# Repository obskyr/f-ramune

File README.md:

# F-Ramune

F-Ramune is a device that lets you test and program 28-pin FRAM chips (e.g. the FM1808 family)! It lets you:

* Test that a chip is genuine FRAM!
* Test that all of the memory cells of an FRAM chip work!
* Identify a memory chip (size, non-volatility, etc.)
* Read from an FRAM chip!
* Write to an FRAM chip!

It features a reprogrammable pushbutton that lets you quickly test chips – out of the box, it's set to check that a chip is 32 KiB of genuine FRAM in full working order – and a serial interface with accompanying software that lets you program your memory chips from your PC.

I made this to test FM1808s of dubious (i.e. cheap Chinese) origin so that the [Game Boy cartridge immortalization mod](https://www.tindie.com/products/obskyr/save-immortalizer-kit-for-game-boy/) would become more feasible and accessible. I expect that to be the main use of F-Ramune, but it's written in an extensible fashion – if you want to test or program FRAM (or SRAM!) in a different form factor or pinout, not much needs to be changed.

## Getting started

Since F-Ramune is a physical device, you'll first need to build that device. Instructions for this can be found in the [hardware directory](hardware) of the repo. At the moment, there's no PCB version, so it's fairly involved – you have to manually route it on stripboard or breadboard – but it's more than doable.

Once you've built the device, you need to upload the firmware to it. For user-friendliness, F-Ramune's firmware is Arduino-based! Open `software.ino` (in the [`software` directory](software)) in the [Arduino IDE](https://www.arduino.cc/en/main/software), set the board to "Arduino Nano", and click the "upload" button. Bam! Your F-Ramune is now ready to go!

## How to test a chip

Put the chip you want to test in the socket. Press the button to test the chip. Out of the box, upon pressing the button, the LEDs will possibly flash back and forth a bit while testing, and finally indicate:

* **Red** if the chip is 32 KiB of genuine FRAM.
* **Red and green** if the chip is genuine, but faulty memory cells were found.
* **Green** if the chip is 32 KiB of genuine FRAM.

The function of the button can be reprogrammed in [`software.ino`](software/software.ino), if you'd like to check for other traits.

## How to program or analyze a chip

Plug the F-Ramune Arduino into your PC, and put the chip you want to test in the socket. Using the command-line program `framune.py` (found in the `software` directory; requires [Python 3](https://www.python.org/downloads/)) , you can read from, write to, and analyze the properties of the chip. Run `framune.py --help` for details.

## Cool!

F-Ramune is just one part of a larger project, and it's fairly niche, so my instructions here are more terse than they usually are. But fear not! If you have any questions, there are any issues, or you just want to talk, you can contact me in the following ways:

* [@obskyr](https://twitter.com/obskyr) on Twitter, or
* [E-mail](mailto:powpowd@gmail.com) me!

For a quick response, writing to me on Twitter is your best bet. If you built F-Ramune, especially, I would *love* to hear about it!

Enjoy! ☆

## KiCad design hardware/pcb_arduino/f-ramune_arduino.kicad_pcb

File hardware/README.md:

# The F-Ramune hardware

As of yet, there's no PCB version of F-Ramune, but here are some instructions for building it on stripboard or breadboard!

The bill of materials is as following:

| Part                             | Description               | Number required |
| ----------------------------     | ------------------------- | --------------- |
| Arduino Nano                     |                           | 1               |
| ZIF Socket with DIP-28 footprint | To fit SMD parts a [SOIC-28 ZIF socket](https://www.adafruit.com/product/1281). To also be compatible with DIP chips, a DIP-28 ZIF socket can be used as the bottom layer in a… socket cake. | 1
| 74HC595                          | 8-bit SIPO shift register | 2               |
| IRL520N                          | N-channel MOSFET          | 1               |
| Green LED                        |                           | 1               |
| Red LED                          |                           | 1               |
| Pushbutton                       |                           | 1               |
| 10 kΩ resistor                   |                           | 1               |
| 100 Ω resistor                   |                           | 1               |
| 330 Ω resistor                   |                           | 2               |

## Tips for all versions

The schematic specifies the transistor to be an IRL520N, but **any N-channel MOSFET with an I<sub>D</sub>** (drain current) **of 200 mA or higher, a V<sub>GS</sub>** (gate threshold) **of 4.5 V or lower and an R<sub>DS(ON)</sub>** (on-resistance) **of 1 Ω or lower works**. The V<sub>GS</sub> requirement is for ~5 V logic signals to work. The R<sub>DS(ON)</sub> of 1 Ω is calculated based on an assumed max supply current for the memory chip of 200 mA and a max allowable voltage drop of 0.2 V (0.2 A / 0.2 V = 1 Ω). Using a more realistic max supply current of 140 mA and/or a more forgiving voltage drop limit, you can arrive at a higher max R<sub>DS(ON)</sub>, and it'll probably still work fine – albeit with less leeway. If you've got MOSFETs lying around, check out their datasheets and see if they're reasonably close to the requirements!

<!-- For the eventual PCB version:
## PCB

### Tips for the PCB version

* The schematic specifies an 18.432 MHz crystal, but if you've got a 16 MHz crystal lying around, you can use that – it'll just make the serial communication less reliable (0% timing error for 18.432 MHz vs. ~3.5% error for 16). This might still work fine, but it's possible it'll cause trouble with some serial adapters. 
-->

## Stripboard

There's no layout diagram for building F-Ramune on stripboard (since apparently there's no good digital stripboard design program!?), but it's a very reliable and permanent way to build it, so why not give it a shot? Using [the schematic](breadboard-schematic.png), you can put together something most respectable. Here's my finished stripboard:

Don't make the mistake I did and leave too little space for the socket – preferably, solder in whatever socket you're using *before* any wires. Measure twice, cut once, y'know?

## Breadboard

I wouldn't recommend breadboarding F-Ramune – breadboards are unreliable, and the device uses high-speed signals and has to be quite picky with voltages. If you would like to try, though, the breadboard schematic and layout can be found in `breadboard.fzz`, which is a [Fritzing](http://fritzing.org/) file. Either install Fritzing and open that file, or take a gander at the image versions of [the schematic](breadboard-schematic.png) and [the layout diagram](breadboard.png). The layout is somewhat optimistically routed, so some spur-of-the-moment re-routings may need to be done as space gets tight. Here's the finished product:

### Tips for breadboarding F-Ramune

* Use a high-quality breadboard! Although FRAM chips consume next to no current, SRAM chips can consume up to 140 mA. Channeling that much via a breadboard with poor connections and bizarrely resistive power rails is a fool's errand – I learned this the hard way.
* If you're using a breadboard of lesser quality, keep the following in mind:
    * When you insert a wire or a pin, make sure it feels like it's being gripped (and before you insert an IC, check those holes with a wire first). If it doesn't, that hole may be intermittent or flat-out broken. You can remedy this by using a different hole on the same row, replacing the strip on that particular row, or [jamming a resistor leg into it](https://twitter.com/obskyr/status/1096047043683012609).
    * You may need to run wires directly to the memory chip's V+ and ground pins from the holes right by the Arduino, since going via the power rails might prove too high-resistance. Adding more bridge wires (like the ones on the far right in the breadboard diagram) may also help, albeit not as much.
* The pins on a TO-220 package such as the MOSFET here are highly destructive to breadboard holes. Use a gripping implement to turn the thin part of the pins 45–90° before inserting it, so the pins don't get gripped lengthwise and bend the breadboard's connectors out of shape.

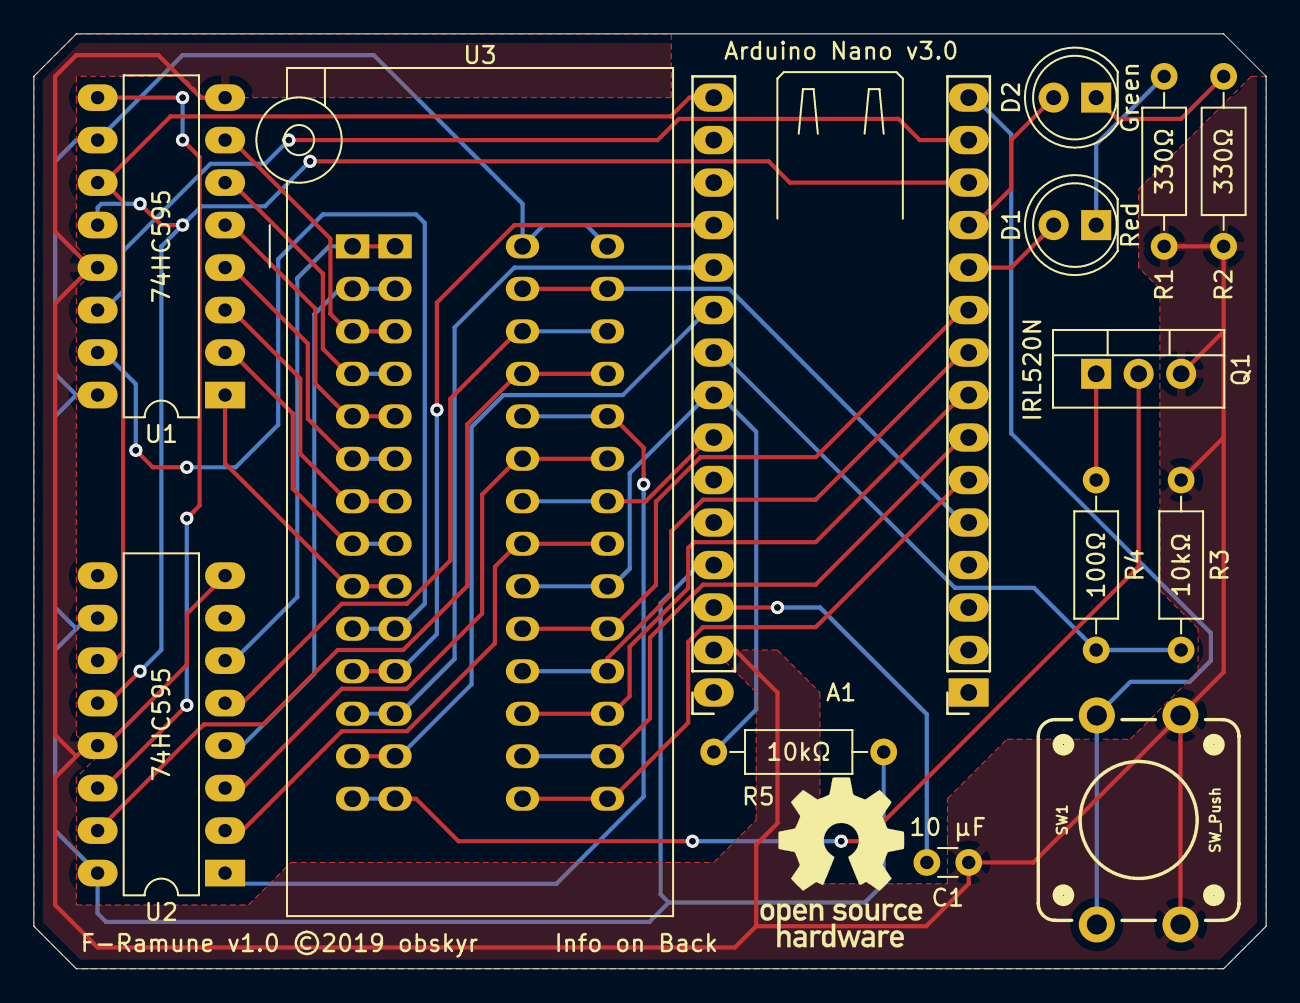
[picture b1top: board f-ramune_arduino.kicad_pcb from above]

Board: 2 copper layers, 73.7 x 55.9 mm, 14 parts (0 on the bottom side), 41 nets.

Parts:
A1: Arduino Nano v3.0; Socket_Strip_Arduino_Nano
C1: 10 µF; C_Disc_D3.0mm_W1.6mm_P2.50mm
D1: Red; LED_D5.0mm
D2: Green; LED_D5.0mm
Q1: IRL520N; TO-220-3_Vertical
R1, R2: 330Ω; R_Axial_DIN0207_L6.3mm_D2.5mm_P10.16mm_Horizontal
R3, R5: 10kΩ; R_Axial_DIN0207_L6.3mm_D2.5mm_P10.16mm_Horizontal
R4: 100Ω; R_Axial_DIN0207_L6.3mm_D2.5mm_P10.16mm_Horizontal
SW1: SW_Push; TACTILE_SWITCH_PTH_12MM
U1, U2: 74HC595; DIP-16_W7.62mm_LongPads
U3: Memory (Socket); ZIF_Socket_DIP-28_With_Alternatives

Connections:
+5V: A1.27, R5.1, U1.10, U1.16, U2.10, U2.16, U3.28
A0: U1.15, U3.10
A1: U1.1, U3.9
A2: U1.2, U3.8
A3: U1.3, U3.7
A4: U1.4, U3.6
A5: U1.5, U3.5
A6: U1.6, U3.4
A7: U1.7, U3.3
A8: U2.15, U3.25
A9: U2.1, U3.24
A10: U2.2, U3.21
A11: U2.3, U3.23
A12: U2.4, U3.2
A13: U2.5, U3.26
A14: U2.6, U3.1
D0: A1.19, U3.11
D1: A1.20, U3.12
D2: A1.21, U3.13
D3: A1.6, U3.15
D4: A1.7, U3.16
D5: A1.8, U3.17
D6: A1.9, U3.18
D7: A1.10, U3.19
GND: A1.29, C1.1, Q1.3, R1.2, R2.2, R3.1, SW1.1, U1.8, U1.13, U2.8, U2.13
Goodnight: A1.22, R3.2, R4.2
unnamed: A1.11, D1.2
unnamed: A1.12, D2.2
unnamed: A1.15, SW1.2
unnamed: A1.28, C1.2
unnamed: D1.1, R1.1
unnamed: D2.1, R2.1
unnamed: Q1.1, R4.1
unnamed: Q1.2, U3.14
unnamed: U1.9, U2.14
SR_Data: A1.14, U1.14
SR_Latch: A1.13, U1.12, U2.12
SR_Shift: A1.16, U1.11, U2.11
~CE: A1.23, R5.2, U3.20
~OE: A1.24, U3.22
~WE: A1.5, U3.27

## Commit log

2019-01-30 Draw schematic.
    Along with adding .gitignore.
2019-01-31 Add Fritzing breadboard diagram.
2019-01-31 Overhaul breadboard to use Arduino Nano.
    Turns out the FM18W08 (as opposed to the regular FM1808) is CMOS logic, which means the lower cutoff for a logical 1 is 3.5V. So... for compatibility, a 3.3V logic MCU needs the ability to switch bet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
2019-01-31 Reroute breadboard a wee bit.
2019-01-31 Nevermind! It was better before.
2019-01-31 Moved FRAM control pins to potentially make way for ICSP.
2019-02-01 Add indicator LEDs and test button to breadboard.
    The ICSP pins be darned for the moment - the breadboard and circuit board versions might as well have different pinouts.
2019-02-02 Reroute breadboard to leave pins 0 and 1 unconnected.
    As it turns out, USB serial goes via pins 0 and 1 on the MCU on the Arduino too, so they can't be connected to other things if serial is used. We're really using ALL the pins! Exciting!
2019-02-09 A whole lot of code!
    A system for arbitrarily implemented IO channels (I may have fallen for overgenericization) and a class for interfacing with memory chips!
    Wow, templates really get messy, don't they? I had to do some seriously impressive somersaults to make separation of API and implementation work both to C++'s and Arduino's constraints at the same ti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
    Oh, and all this is entirely untested. I haven't had the parts to test until just the other day - I've been writing code in the dark. So that's next up, I suppose.
2019-02-09 Fix shifting out too many bits.
    That should be "--", not "++"!
2019-02-11 Code galore!
    Lots of fixes (the Arduino IDE lets you turn on -Wall!) and huge optimization. Still isn't fast enough, though.
    Oh, and there's still the minor case of this major bug... https://stackoverflow.com/questions/54632425/is-casting-derived-%e2%86%92-base-wrong-whats-the-alternative
2019-02-11 Fix ChannelSet compatibility.
    Using templates! Wow!
2019-02-11 Strip API testing code.
2019-02-12 Interface with address shift register via SPI.
    This makes the address setup bizarrely fast, apparently! Good stuff!
2019-02-12 Rename project to f-ramune!
    Enough work has gone into this that it shouldn't have a generic name.
2019-02-13 Add testing code, fix bugs, live life.
2019-02-14 Initialize control pins properly; change test interface.
    So THAT'S why it seemed like data wasn't persisting across resets. When I was trying to read data back, WE was low, which actually performed a write...
2019-02-14 Fix memory potentially being inadvertently written to.
    Memory control pins should start high (inactive), and a pull-up on CE makes sure the memory chip isn't enabled when the control pins are unconfigured.
    Oh, and I flipped a transistor which was the wrong way in the schematic. Whoops!
2019-02-15 Fancify test interface a li'l bit.
2019-02-18 Use a low-side MOSFET for switching on/off the memory chip.
    Wow, geez, there are a lot of considerations to be made when cutting power to an IC! This commit implements and explains a whole lot of those.
    The main reason for using a MOSFET over a BJT is that BJTs have fairly high voltage drop, which could potentially be troublesome.
2019-02-18 Move breadboard chips to the left one row.
    Just a liiiittle bit more compact.
2019-02-20 Use internal pull-up resistor for button.
    Turns out the MISO pin, even when overridden to be an input by the SPI peripheral, can use the internal pull-up. That makes one less component!
2019-02-28 Start of the serial interface.
2019-03-01 Add "set memory chip" serial command.
    Along with a few miscellaneous bug fixes and additions.
2019-03-01 Make chip analysis work *mwah* just like-a mama used to make.
    Along with integrating chip analysis into the "set chip command" and miscellaneous fixes and such.
2019-03-01 Add software gitignore.
2019-03-01 Finally implement that test button!!!
    You know that test button that really was the entire point of the device? The whole idea? After a bunch of bells and whistles (and a... serial interface!?), it finally does what it set out to do!!!
2019-03-06 KiCAD version of Arduino schematic.
    Along with a li'l bit of restructuring.
2019-03-08 Add read command.
2019-03-08 Make MemoryChip attributes update F-Ramune when manually set.
2019-03-09 Add write command; fix bugs.
    That's all the commands!
2019-03-09 Add a CLI for half the commands.
2019-03-09 Add a CLI for the read and write commands!
    And with that, the software is full-fledged! CLI interfacin' with FRAM and SRAM? Sure, why not!
    (...EEPROM speed still isn't implemented, but eh. Meh. Eh meh.)
2019-03-28 Have memory chip unpowered during downtime.
    This way, you won't have to switch out the chip while it's powered, which might cause serious trouble.
2019-03-28 Test entire address space!
    Now you can be absolutely sure that the chip you're testing is going to work 100% fine.
2019-04-16 Pictures and instructions!
    That PCB version has to wait. A guy's gotta have priorities, you know?
2019-04-17 Add a PCB version based on the Arduino stripboard F-Ramune. Should be fabricated on blue soldermask for best results.
2019-04-17 Add more silkscreen indicators onto the board to make it easier to assemble.
2019-04-17 Built gerber files, ready for prototype production! (No BOM though...)
2019-04-18 Last-minute silkscreen changes to indicate LED colors and Arduino orientation. Also, delete the redundant NPTH file as this design only has plated holes.
    It's called last-minute, because the cutoff for changes to my PCB order is 2 hours from now and I just noticed the design issue.
2019-04-20 Here's a schematic for a bare-AVR version of F-Ramune, including in-circuit programming functionality (do not use with native USB)
2019-05-24 The pin assignments on this switch footprint are wrong. The switch does not close between the long side of the part's pins - it closes around the short side.
2019-05-24 Also, here's an almost-full SMD AVR version of F-Ramune that will probably never be assembled
2019-05-25 Improve the interface of framune.py a li'l bit.
2019-05-25 Extend delay after powering on chip.
    To support... bizarre FRAM chips that just need a bit to get ready once they've been turned on, for some reason? Very very strange.
    I also took the chance to remove a line of test code I'd forgotten to remove before.
2019-05-25 Fix incorrect copyright date on AVR silkscreen.
2019-05-25 Add Gerbers for the AVR/SMD version of F-Ramune.
2019-05-25 Update / tidy up the Arduino version and add the instructions on the back
2021-03-09 Add link
    Link never came, figured I'd help it along 😛

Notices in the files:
hardware/pcb_arduino/f-ramune_arduino.kicad_pcb:
F-Ramune v1.0 ©2019 obskyr https://github.com/obskyr/f-ramune
F-Ramune v1.0 ©2019 obskyr Info on Back
